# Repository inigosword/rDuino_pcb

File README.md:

# rDuino_pcb
gerber pcb layout for rDuino astronomy tracker

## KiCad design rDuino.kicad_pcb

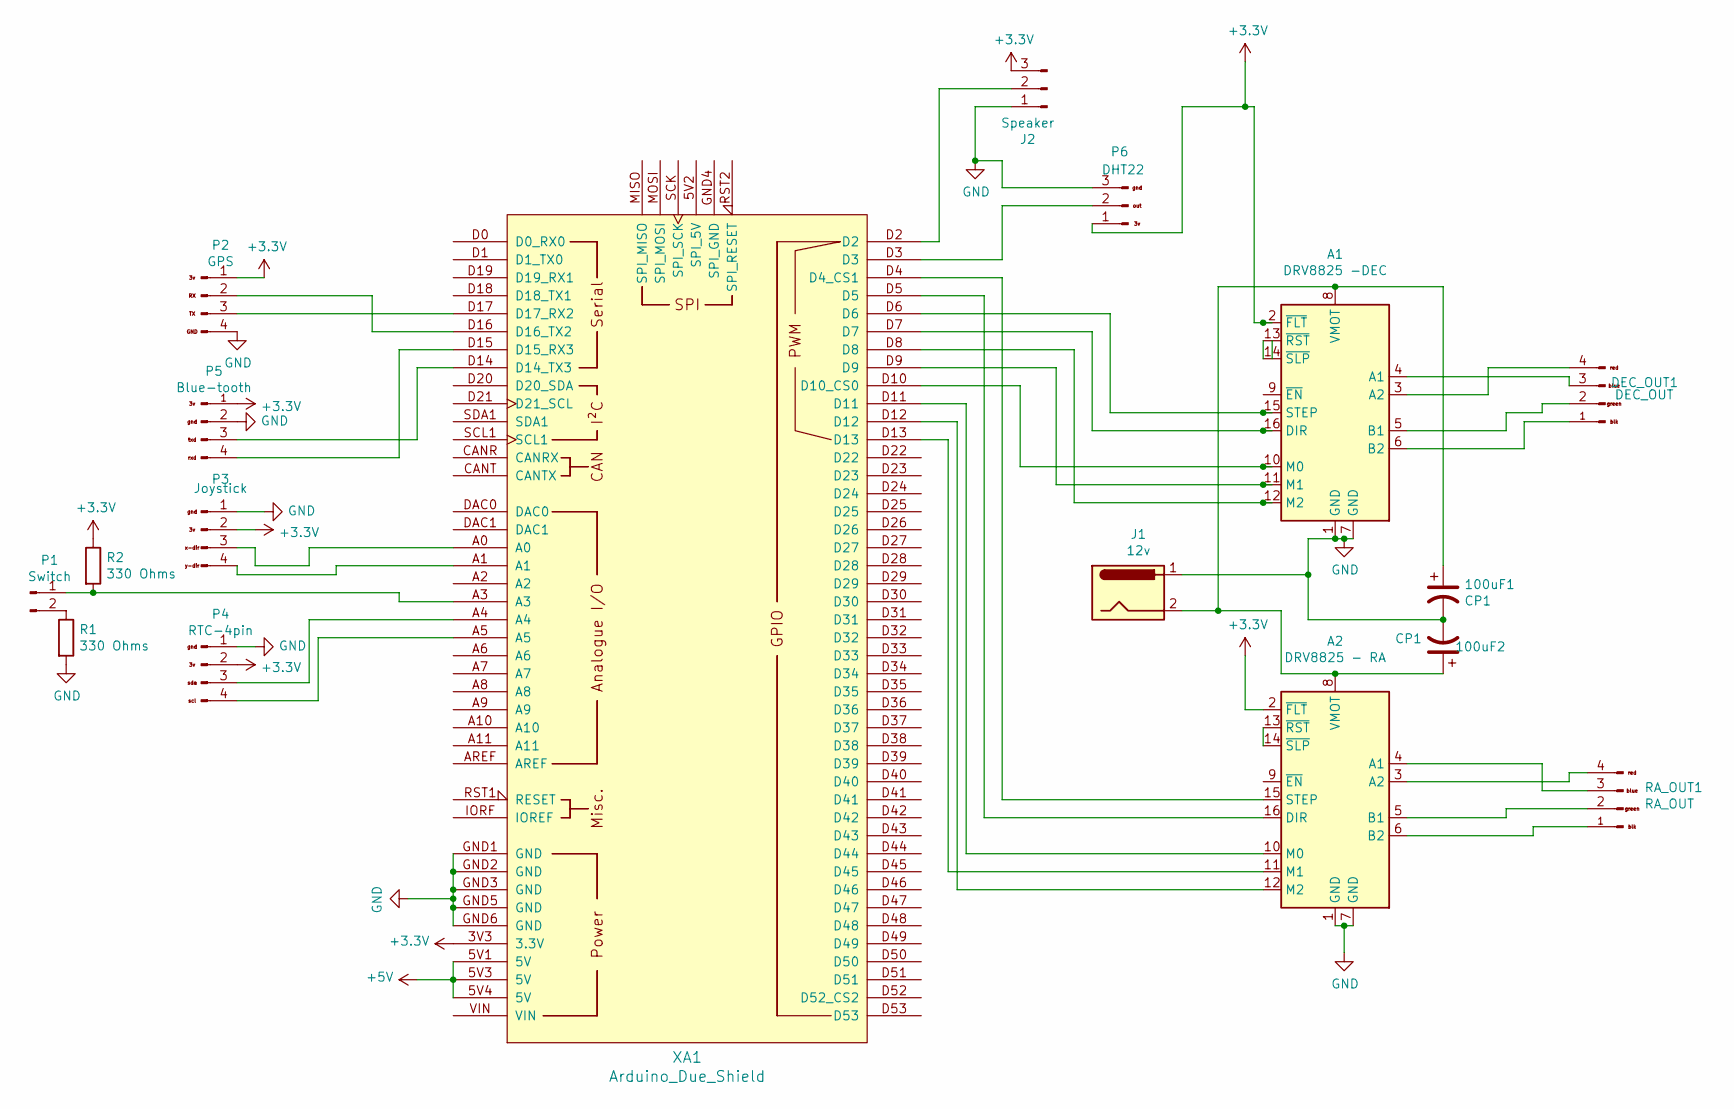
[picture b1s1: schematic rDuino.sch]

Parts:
100uF1, 100uF2: CP1; CP_Radial_D8.0mm_P5.00mm
A1: DRV8825 -DEC; Pololu_Breakout-16_15.2x20.3mm
A2: DRV8825 - RA; Pololu_Breakout-16_15.2x20.3mm
DEC_OUT1: DEC_OUT; PinHeader_1x04_P2.54mm_Vertical
J1: 12v; BarrelJack_CUI_PJ-063AH_Horizontal
J2: Speaker; PinHeader_1x03_P2.54mm_Vertical
P1: Switch; PinHeader_1x02_P2.54mm_Vertical
P2: GPS; PinHeader_1x04_P2.54mm_Vertical
P3: Joystick; PinHeader_1x04_P2.54mm_Vertical
P4: RTC-4pin; PinHeader_1x04_P2.54mm_Vertical
P5: Blue-tooth; PinSocket_1x04_P2.54mm_Vertical
P6: DHT22; PinHeader_1x03_P2.54mm_Vertical
R1, R2: 330 Ohms; R_Axial_DIN0204_L3.6mm_D1.6mm_P2.54mm_Vertical
RA_OUT1: RA_OUT; PinHeader_1x04_P2.54mm_Vertical
XA1: Arduino_Due_Shield

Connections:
+3V3: A1.2 (~FLT), A2.2 (~FLT), J2.3, P2.1, P3.2, P4.2, P5.1, P6.1, R2.1, XA1.3V3 (3.3V)
+5V: XA1.5V1 (5V), XA1.5V3 (5V), XA1.5V4 (5V)
GND: 100uF1.2, 100uF2.2, A1.1 (GND), A1.7 (GND), A2.1 (GND), A2.7 (GND), J1.1, J2.1, P2.4 (GND), P3.1, P4.1, P5.2, P6.3, R1.2, XA1.GND1 (GND), XA1.GND2 (GND), XA1.GND3 (GND), XA1.GND5 (GND), XA1.GND6 (GND)
unnamed: 100uF1.1, 100uF2.1, A1.8 (VMOT), A2.8 (VMOT), J1.2
unnamed: A1.3 (A2), DEC_OUT1.4
unnamed: A1.4 (A1), DEC_OUT1.3
unnamed: A1.5 (B1), DEC_OUT1.2
unnamed: A1.6 (B2), DEC_OUT1.1
unnamed: A1.10 (M0), XA1.D10 (D10_CS0)
unnamed: A1.11 (M1), XA1.D9
unnamed: A1.12 (M2), XA1.D8
unnamed: A1.13 (~RST), A1.14 (~SLP)
unnamed: A1.15 (STEP), XA1.D6
unnamed: A1.16 (DIR), XA1.D7
unnamed: A2.3 (A2), RA_OUT1.4
unnamed: A2.4 (A1), RA_OUT1.3
unnamed: A2.5 (B1), RA_OUT1.2
unnamed: A2.6 (B2), RA_OUT1.1
unnamed: A2.10 (M0), XA1.D11
unnamed: A2.11 (M1), XA1.D13
unnamed: A2.12 (M2), XA1.D12
unnamed: A2.13 (~RST), A2.14 (~SLP)
unnamed: A2.15 (STEP), XA1.D4 (D4_CS1)
unnamed: A2.16 (DIR), XA1.D5
unnamed: J2.2, XA1.D2
unnamed: P1.1, R2.2, XA1.A3
unnamed: P1.2, R1.1
unnamed: P2.2, XA1.D16 (D16_TX2)
unnamed: P2.3, XA1.D17 (D17_RX2)
unnamed: P3.3, XA1.A0
unnamed: P3.4, XA1.A1
unnamed: P4.3, XA1.A4
unnamed: P4.4, XA1.A5
unnamed: P5.3, XA1.D14 (D14_TX3)
unnamed: P5.4, XA1.D15 (D15_RX3)
unnamed: P6.2, XA1.D3

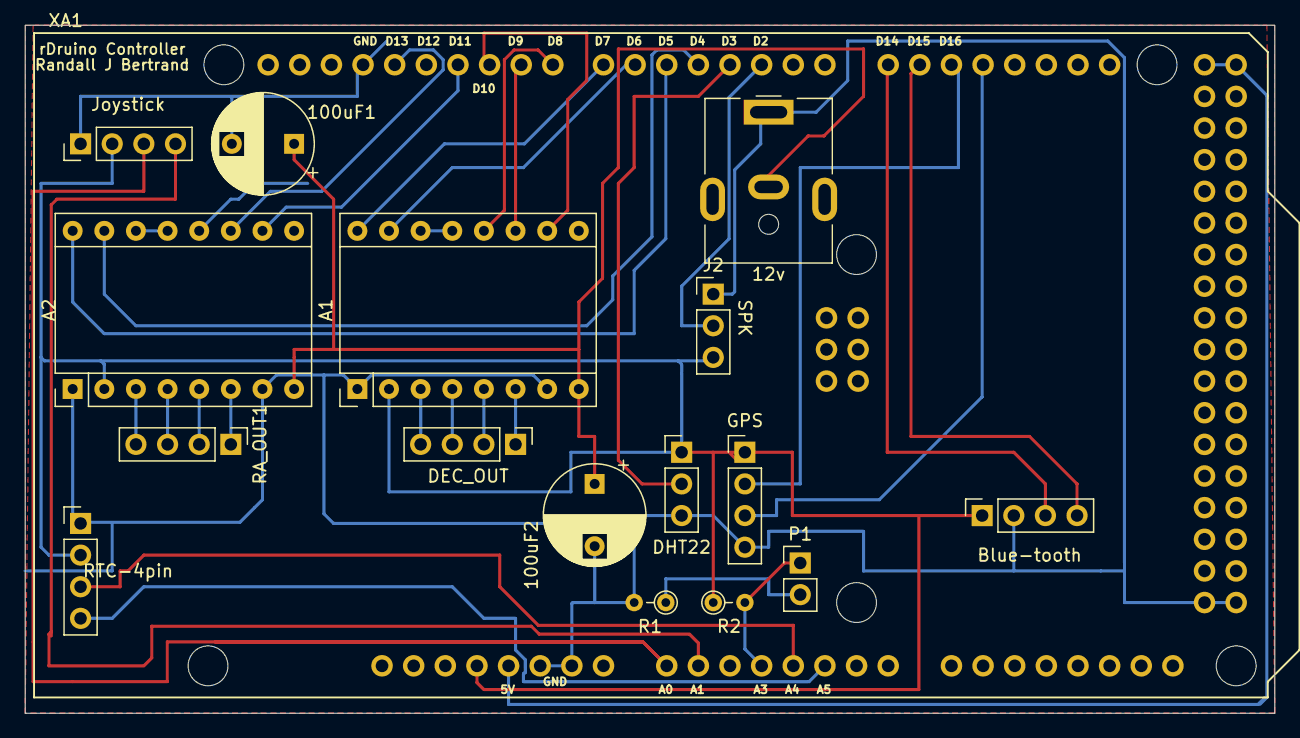
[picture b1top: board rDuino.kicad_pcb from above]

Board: 2 copper layers, 100.3 x 55.2 mm, 17 parts (0 on the bottom side), 36 nets.

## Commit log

2021-01-23 spk update

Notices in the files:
rDuino.sch:
creativecommons.org/licenses/by/4.0
Lincense CC by 4.0
